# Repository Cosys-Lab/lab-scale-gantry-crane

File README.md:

# Lab-scale Gantry Crane Digital Twin Exemplar

This repository describes a lab-scale gantry crane digital twin exemplar. This exemplar was used in a couple of our [publications](#publications). This readme only contains basic information, for the complete documentation, head to [github pages](https://Cosys-Lab.github.io/lab-scale-gantry-crane/).

The repository is structured as follows:

- [BOM](BOM/): the Bill-of-Materials of the crane.
- [C4-diagrams](C4-diagrams/): C4 diagrams of the crane's software used in the EDTConf submitted exemplar paper.
- [CAD](CAD/): CAD models of the crane in Fusion360, as well as 3MF exports for 3D printing.
- [arcadia](arcadia/): Capella models of the crane used in the SpaceRaise doctoral school.
- [arduino](arduino/): KiCad project of an optional Arduino shield that simplifies connecting the sensors of the crane, and accompanying code.
- [docker](docker/): A Docker compose file and associated files allowing for easy setup of the necessary background services.
- [docs](docs/): docs for creating the GitHub pages with MkDocs
- [examples](examples/): Examples of the Python module that controls the crane.
- [gantrylib](gantrylib/): The Python module controlling and monitoring the crane.
- [tests](tests/): Tests of the gantrylib module.

## Hardware Quickstart

Refer to the [build guide](https://cosys-lab.github.io/lab-scale-gantry-crane/build/) on GitHub Pages.

## Software Setup

### Python

Install Python. On Windows, preferably use Python 3.13 or higher, since earlier versions have a low resolution (only 15.6 ms) of the `time()` and `datetime.now()` functions, which are used often in the code.

Install the `gantrylib` module locally as editable installation. From the root of the repository folder, run:

    python -m pip install -e .

### Background services

The software relies on a TimescaleDB database, a Grafana dashboard and, optinally an MQTT broker. The setup files of all of these are contained in the [docker](docker/) folder. Assuming docker and docker compose are installed, from the docker folder, it suffices to run:

    docker compose up

The containers can then be started and stopped with:

    docker compose stop
    docker compose start

To remove the containers and the network connecting them, run:

    docker compose down

The config is exceptionally insecure, since all of the default usernames/passwords are used. If this is a problem, do change them.

#### TimeScaleDB
- address: localhost
- port: 5432
- user: postgres
- password: postgres
- database: gantrycrane

#### Grafana Dashboard
- address: localhost
- port: 3000
- user: admin
- password: admin (On first login via http://localhost:3000, you will be prompted to change the password. Nothing blocks you from reusing the old password though.)

#### MQTT
- address: localhost
- port: 1883
- user: not necessary, anonymous connections are allowed

The MQTT broker is really only needed if you want to run the TrajectoryGenerator service in its MQTT mode. Ofter services (Simulator, Validator) have in this release not yet been implemented in MQTT mode.

## Software quickstart

Assuming you went through the [software setup](#software-setup) and built the crane according to the [hardware quickstart](#hardware-quickstart), the fastest way to get the crane to do something is using the [run_with_hmi.py](examples/run_with_hmi.py) example. A short video demonstrating the example can be found on [youtube](https://youtu.be/BBAWoA0mC9U).

You will have to configure [crane-properties.yaml](examples/crane-properties.yaml) for your specific installation, more specifically, specify the serial ports of the two motor controller boards. Unfortunately, the Trinamic devkits don't offer a unique ID that allows you to identify them, therefore we recommend plugging in the boards one by one, and noting down the serial ports that appear as you plug them in (in `device manager/Ports (COM & LPT)` in Windows, or under `/dev/tty*` in Linux.)

Once you have noted down those ports, update the following two fields in the config:

    cart_motor_port: COM13
    ...
    hoist_motor_port: COM8

You can now run the example.

Upon first starting, it will home the cart and hoist motor. Homing the cart motor happens automatically, homing the hoist motor must be done with some manual user input. The script prompts you to confirm this on the command line. Afterwards you will see the simple HMI interface that allows you to move the crane.

## Publications

Below are publications in which this exemplar was used:

1. J. Mertens and J. Denil, *Localizing Faults in Digital Twin Models by Using Time Series Classification Techniques*, 2024 Winter Simulation Conference (WSC), IEEE, Dec. 2024, pp. 2868–2879. [https://doi.org/10.1109/wsc63780.2024.10838825](https://doi.org/10.1109/wsc63780.2024.10838825)

2. J. Mertens, S. Klikovits, F. Bordeleau, J. Denil, and Ø. Haugen, *Continuous Evolution of Digital Twins using the DarTwin Notation*, Software and Systems Modeling, p. 22, Nov. 2024. [https://doi.org/10.1007/s10270-024-01216-7](https://doi.org/10.1007/s10270-024-01216-7)

3. J. Mertens and J. Denil, *Reusing model validation methods for the continuous validation of digital twins of cyber-physical systems*, Software and Systems Modeling, p. 23, Oct. 2024. [https://doi.org/10.1007/s10270-024-01225-6](https://doi.org/10.1007/s10270-024-01225-6)

4. J. Mertens and J. Denil, *Digital-twin Co-evolution using Continuous Validation*, In Proceedings of the ACM/IEEE 14th International Conference on Cyber-Physical Systems (with CPS-IoT Week 2023), ICCPS ’23, San Antonio, TX, USA: ACM, 2023, pp. 266–267. [https://doi.org/10.1145/3576841.3589628](https://doi.org/10.1145/3576841.3589628)

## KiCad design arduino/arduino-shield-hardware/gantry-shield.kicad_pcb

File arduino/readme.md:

# Arduino

We use an Arduino Uno for monitoring and controlling the angle measuring encoder, the anemometer, the electromagnet (and the fischertechnik conveyor belt).

The folders contain:

- [arduino-shield-hardware](arduino-shield-hardware/)  
  The KiCad files of the optional Arduino shield.
- [arduino-shield-software](arduino-shield-software/)  
  The software to flash on the Arduino.
- [mqtt-wrapper](mqtt-wrapper/)  
  An MQTT wrapper around the Serial interface of the Arduino. Not needed when you only want to monitor the sensors.

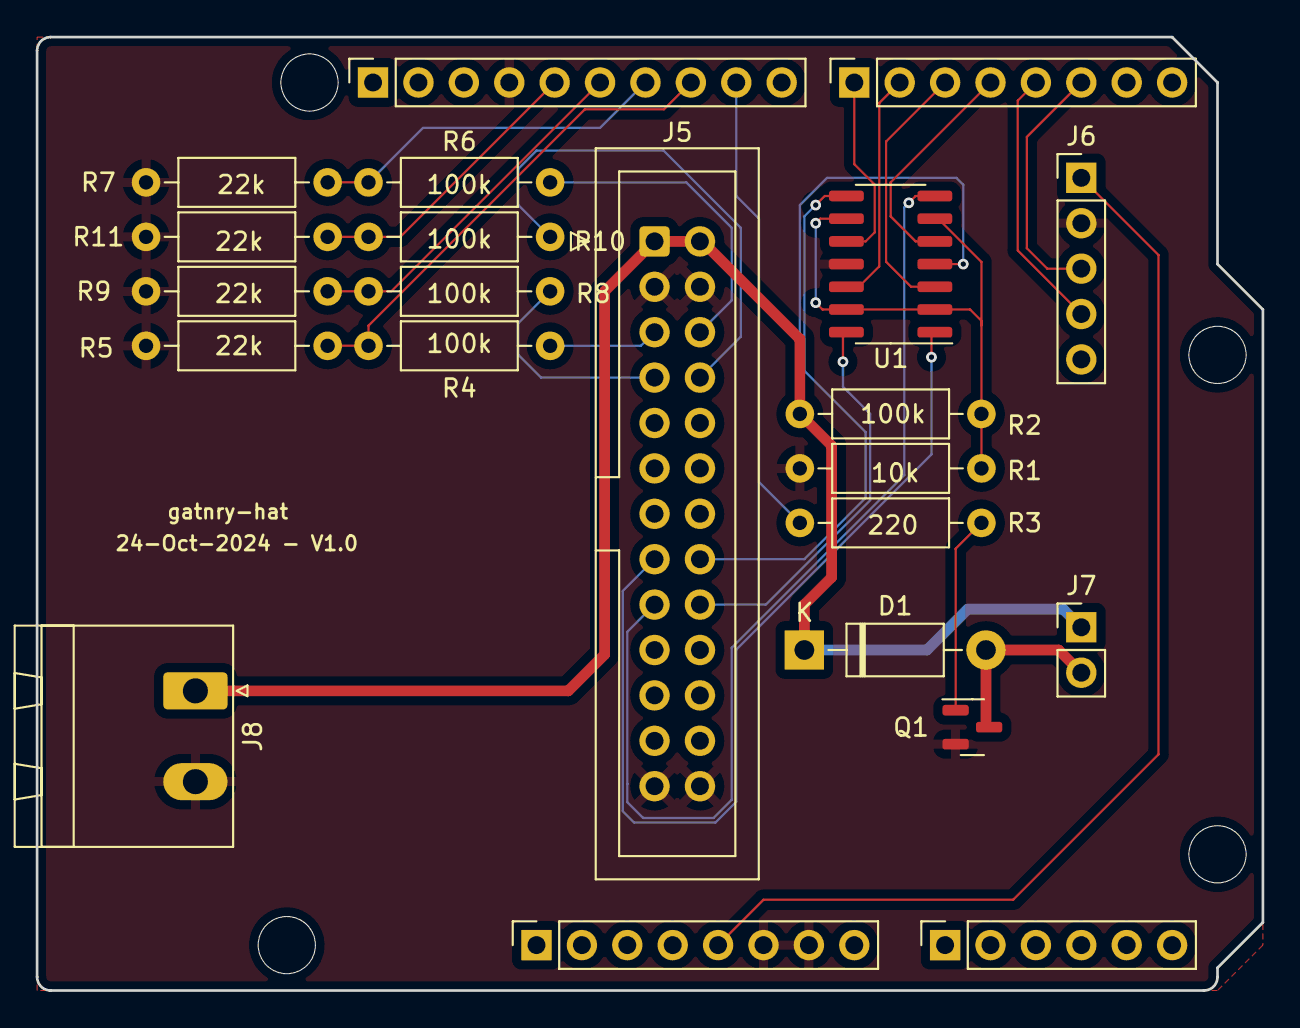
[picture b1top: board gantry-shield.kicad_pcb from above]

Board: 2 copper layers, 68.6 x 53.3 mm, 26 parts (0 on the bottom side), 25 nets.

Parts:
D1: 1N4007; D_DO-41_SOD81_P10.16mm_Horizontal
J1: Power; PinSocket_1x08_P2.54mm_Vertical
J2: Digital/PWM; PinSocket_1x10_P2.54mm_Vertical
J3: Analog; PinSocket_1x06_P2.54mm_Vertical
J4: Digital/PWM; PinSocket_1x08_P2.54mm_Vertical
J5: Conn_02x13_Odd_Even; IDC-Header_2x13_P2.54mm_Vertical
J6: encoder; PinHeader_1x05_P2.54mm_Vertical
J7: electromagnet; PinHeader_1x02_P2.54mm_Vertical
J8: 24V input; PhoenixContact_MSTBA_2,5_2-G-5,08_1x02_P5.08mm_Horizontal
MH1, MH2, MH3, MH4: MountingHole_3.2mm
Q1: BS170F; SOT-23
R1: 10k; R_Axial_DIN0207_L6.3mm_D2.5mm_P10.16mm_Horizontal
R2, R4, R6, R8, R10: 100k; R_Axial_DIN0207_L6.3mm_D2.5mm_P10.16mm_Horizontal
R3: 220; R_Axial_DIN0207_L6.3mm_D2.5mm_P10.16mm_Horizontal
R5, R7, R9, R11: 22k; R_Axial_DIN0207_L6.3mm_D2.5mm_P10.16mm_Horizontal
U1: TL084; SOIC-14_3.9x8.7mm_P1.27mm

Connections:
+5V: J1.5, J6.1
+24V: D1.1 (K), J5.1, J5.2, J7.1, J8.1, R2.1, U1.4 (V+)
/2: J4.6, J6.3
/4: J4.4, U1.5 (+)
/7: J4.1, U1.10 (+)
/12: J2.6, R8.2, R9.1
/13: J2.5, R10.2, R11.1
/*3: J4.5, J6.4
/*5: J4.3, U1.3 (+)
/*6: J4.2, U1.12 (+)
/*9: J2.9, R3.1
/*10: J2.8, R4.2, R5.1
/*11: J2.7, R6.2, R7.1
/I1: J5.5, R4.1
/I2: J5.6, R6.1
/I3: J5.7, R8.1
/I4: J5.8, R10.1
/Q1: J5.15, U1.1
/Q2: J5.16, U1.8
/Q3: J5.17, U1.7
/Q4: J5.18, U1.14
GND: J1.6, J1.7, J2.4, J5.3, J5.4, J5.25, J5.26, J6.2, J8.2, Q1.2 (S), R1.2, R5.2, R7.2, R9.2, R11.2, U1.11 (V-)
unnamed: D1.2 (A), J7.2, Q1.3 (D)
unnamed: Q1.1 (G), R3.2
unnamed: R1.1, R2.2, U1.2 (-), U1.6 (-), U1.9 (-), U1.13 (-)

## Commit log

2025-01-29 Upload CAD source files
2025-01-29 Upload CAD 3MF exports
2025-01-29 Upload arduino angle measurement sketch
2025-01-29 Upload initial gantrylib package
2025-01-29 Upload initial gantry controller example
2025-01-29 Add BOM
2025-01-29 Update gitignore for KiCad
2025-01-29 Add KiCad files for Arduino shield
2025-01-29 Update BOM
2025-01-29 Add initial Docs
2025-01-30 Turn gantrylib into installable package
2025-01-30 Move trajectory generator main code to separate example
2025-01-30 Remove unused imports
2025-01-30 Remove reference to printers
2025-01-30 Add trajectory generator example
2025-01-30 Add documentation
2025-01-30 Add vscode launch config
2025-01-30 Remove MQTT code
2025-01-30 Update docstrings
2025-01-30 Update docs
2025-01-31 Write crane docstring
2025-01-31 Move GantryController in gantrylib. Add docstrings
2025-01-31 Update trajectory generator docstring
2025-01-31 Update index
2025-01-31 Split up gantry controller example
2025-01-31 Add database writeout again
2025-01-31 Add docstrings to examples
2025-01-31 Add arduino documentation.
2025-01-31 Add arduino documentation
2025-01-31 Update build info
2025-01-31 Update about
2025-01-31 Deployed 4efe6f9 with MkDocs version: 1.6.1
2025-05-06 Add database initialization scripts
2025-05-08 Add docker-compose file
2025-05-08 Add windspeed sensor to Arduino
2025-05-08 Add calibration script (deprecated)
2025-05-08 Add script to populate cargomanifest
2025-05-08 Update database readme
2025-05-08 Add HMI
2025-05-08 Update Arduino code to send uncompressed floats
2025-05-08 Updates to HMI and backend code
2025-05-09 Update HMI
2025-05-09 Update backend
2025-05-15 Initial capella models
2025-05-15 Update PAB
2025-05-15 Update uarttest and arduino-shield
2025-05-15 Update Capella Models
2025-06-06 Push some changes
2025-06-10 Update of Capella models
2025-06-10 First parts of overhaul of trajectory generator
2025-06-11 Move db init files and configure docker compose
2025-06-11 Fix mostquitto conf in docker compose
2025-06-11 Fix grafana provisioning
2025-06-11 Update docker compose readme
2025-06-12 Update and test trajectory generator, factory and mqtt related classes
2025-06-12 Initial work on updated database writing
2025-06-16 Updates to controller for new database writer
2025-06-17 Add continuous logging and tests of that continuous logging
2025-06-18 Update continuous database writing
2025-06-18 Update database init scripts
2025-06-18 Bunch of fixes in the continuous logger.
2025-06-19 Update docker compose for grafana logging rate
2025-06-19 Update logger example
2025-06-26 Add drawio C4 diagram
2025-06-30 Move crane Arduino to separate class
2025-06-30 Wrote test for crane_io_uc
2025-07-04 Bunch of updates
2025-07-07 Add pausing/resuming of continuous logging
2025-07-07 Update limits in HIM
2025-07-07 Test and correct all movements
2025-07-07 fix db writeout
2025-07-08 Fix continuous logging and thread safety
2025-07-08 Folder structure update
2025-07-08 Update repo readme
2025-07-08 Update readme title
2025-07-08 example cleanup
2025-07-08 Add validator and simulator scripts
2025-07-08 Work on simulator and validator
2025-07-09 Add simulator
2025-07-09 Fix broken parallel simulator
2025-07-09 Add validator
2025-07-09 Update properties
2025-07-09 Update readme with video
2026-03-06 Bugfix to run completely without database
